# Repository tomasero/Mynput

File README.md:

#Mynput
    An Interactive PC Game Controller

###Game
[Color Quest](http://redbluegames.com/game-off-2013/)

###Team
- Lauren Farrell
- Bill Kim
- Tomás Vega

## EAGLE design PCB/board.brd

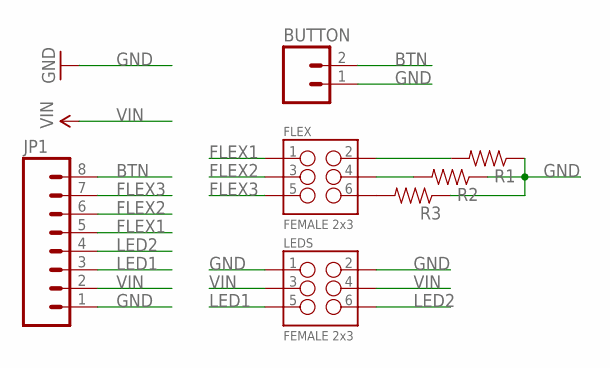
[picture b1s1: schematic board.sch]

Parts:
BUTTON: M02PTH; 1X02
FLEX: FEMALE 2x3; 2X3
JP1: M08NO_SILK_FEMALE_PTH; 1X08_NO_SILK
LEDS: FEMALE 2x3; 2X3
R1, R2, R3: RESISTORPTH-1/4W; AXIAL-0.4

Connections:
BTN: BUTTON.2, JP1.8
FLEX1: FLEX.1, JP1.5
FLEX2: FLEX.3, JP1.6
FLEX3: FLEX.5, JP1.7
GND: BUTTON.1, JP1.1, LEDS.1, LEDS.2, R1.P$1 (1), R2.P$1 (1), R3.P$1 (1)
LED1: JP1.3, LEDS.5
LED2: JP1.4, LEDS.6
R1: FLEX.2, R1.P$2 (2)
R2: FLEX.4, R2.P$2 (2)
R3: FLEX.6, R3.P$2 (2)
VIN: JP1.2, LEDS.3, LEDS.4

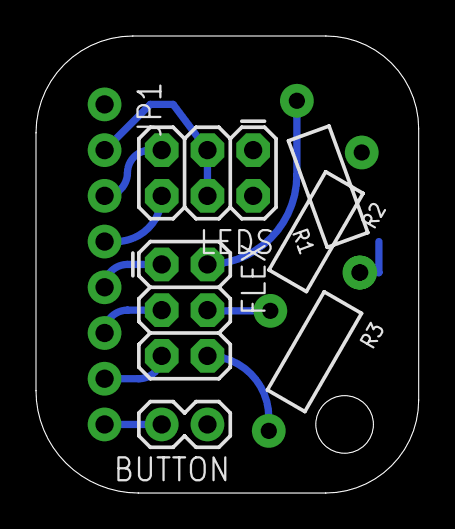
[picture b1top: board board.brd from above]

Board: 2 copper layers, 21.3 x 25.4 mm, 7 parts (0 on the bottom side), 11 nets.

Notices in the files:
parts and their libraries:
SparkFun-Connectors: Licensing: Creative Commons ShareAlike 4.0 International - https://creativecommons.org/licenses/by-sa/4.0
